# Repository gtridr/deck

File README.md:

# deck
An integrated instrument &amp; control surface based on norns

## Credits & Licensing

Starting things off: this project is licensed as a derivative work under GPL-3.0. All due credits to the following individuals & projects:

 - The core audio codec & voltage regulation design are unmodified from the 210330 revision of the [norns shield](https://github.com/monome/norns-shield) save for some rerouting & cleanup

 - The raspberry pi image is a very lightly modified fork of the mainline norns codebase, with just a few tweaks to map the 4th encoder, serial pins for MICROMIDITRS, and soft shutdown via ATXRaspi.

 - The teensy firmware is a fork of Okyeron's [DIY grid](https://github.com/okyeron/neotrellis-monome) firmware. All credit for the grid emulation goes to him; I've only added what was necessary to get the potentiometers working over USB MIDI

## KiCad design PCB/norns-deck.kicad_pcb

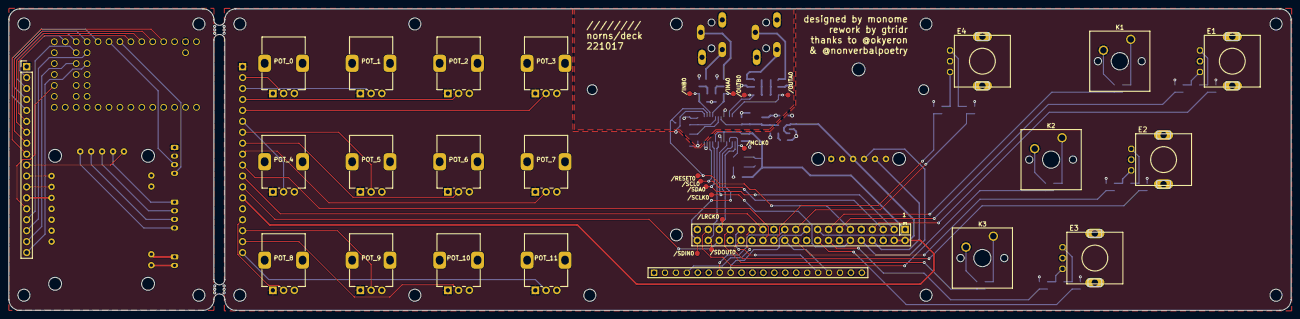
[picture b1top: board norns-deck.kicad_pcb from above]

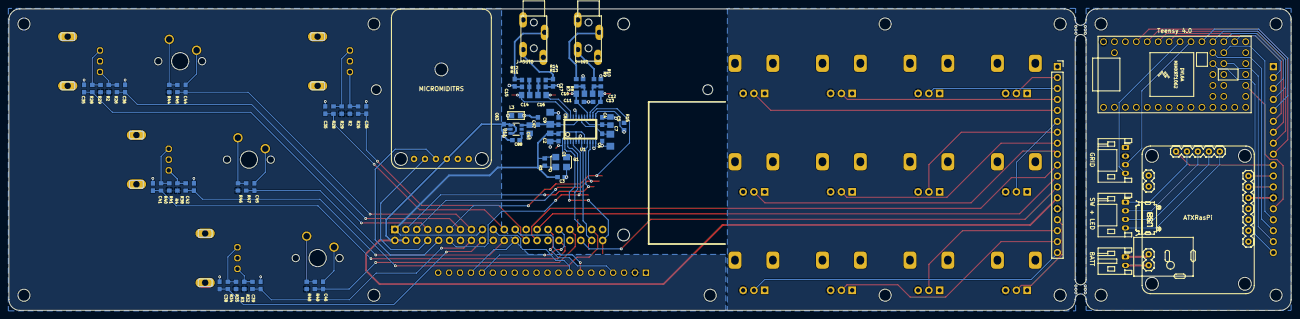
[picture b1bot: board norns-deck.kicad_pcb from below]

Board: 2 copper layers, 297.8 x 70.0 mm, 118 parts (76 on the bottom side), 80 nets.

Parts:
/INA0: TPTP12R; TP12R
/INB0: TPTP12R; TP12R
/LRCK0: TPTP12R; TP12R
/MCLK0: TPTP12R; TP12R
/OUTA0: TPTP12R; TP12R
/OUTB0: TPTP12R; TP12R
/RESET0: TPTP12R; TP12R
/SCL0: TPTP12R; TP12R
/SCLK0: TPTP12R; TP12R
/SDA0: TPTP12R; TP12R
/SDIN0: TPTP12R; TP12R
/SDOUT0: TPTP12R; TP12R
ATXRasPi: ATXRaspi
BATT: JST_PH_S2B-PH-K_1x02_P2.00mm_Horizontal
C1, C4, C6, C8, C47, C63: 100n; C0603
C2, C5, C10, C12, C43: 10u; C0805
C3, C35, C35#2, C36, C36#2, C38, C39, C41, C42, C44, C45, C46, C88: 10n; C0603
C7, C9: 47u; C1206
C11, C13: 220p COG; C0603
C14, C16: 3.3u; C0805
C15, C17: 2700p COG; C0603
DAUGHTERBOARD: PinSocket_1x18_P2.54mm_Vertical
E1: ENC1; PEC11RN
E2: ENC2; PEC11RN
E3: ENC3; PEC11RN
E4: ENC4; PEC11RN
GRID: JST_PH_S4B-PH-K_1x04_P2.00mm_Horizontal
J-IN0: JACK-TRS-SW; JACK4832.2330
J-OUT0: JACK-TRS-SW; JACK4832.2330
K1, K2, K3: SW_Cherry_MX_1.00u_PCB_NO_OUTLINE; SW_Cherry_MX_1.00u_PCB_NARROW_OUTLINE
L3: FERRITE; L0805
MICROMIDITRS: MICROMIDITRS
MNT: mounting hole
MNT#2, MNT#3, MNT#4, MNT#5, MNT#6: mounting hole
POT_0, POT_1, POT_2, POT_3, POT_4, POT_5, POT_6, POT_7, POT_8, POT_9, POT_10, POT_11: Potentiometer_Alps_RK09K_Single_Vertical
Q1: ASFL-12.288mhz; ASF
R1, R2, R2#2, R3, R4, R8, R10, R11, R13, R15, R26, R26#2, R28, R28#2, R29, R29#2, R32, R34, R35, R38, R40, R41, R44, R45, R46, R47, R48, R49: 10k; R0603
R7, R9: 4.99k; R0603
R12, R14: 590; R0603
SW + LED: JST_PH_S4B-PH-K_1x04_P2.00mm_Horizontal
Teensy 4.0: Teensy 4.0; Teensy40
U1: CS4270; TSSOP24
U11: TPS793; SSOP6
U$1: OLED128X64; OLED-ALEPH
X1: RASPI_BOARD_B+#_E3; RASPI_BOARD_B+_EDGES_3DRILL
mouse-bite-2.54mm-slot, mouse-bite-2.54mm-slot#2: VAL**; mouse-bite-2.54mm-slot

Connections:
+3V3: C1.1, C2.1, C3.1, Q1.4, R1.1, R2.2, R2#2.2, R3.2, R4.2, R29.2, R29#2.2, R35.2, R41.2, R44.1, R46.1, R48.1, U1.5, U1.8, U$1.2, X1.1, X1.17
+5V: ATXRasPi.9, C63.1, DAUGHTERBOARD.13, GRID.2, MICROMIDITRS.3, Teensy 4.0.33, U11.1, U11.3, X1.2, X1.4
A1: C35#2.1, R28#2.2, X1.7
A2: C41.1, R40.2, X1.32
A3: C38.1, R34.2, X1.18
A4: C35.1, R28.2, X1.21
A5V: C8.1, C9.1, C43.1, C47.1, U1.19, U11.6
AGND: C4.2, C5.2, C6.2, C7.2, C8.2, C9.2, C11.2, C13.2, C15.2, C17.2, C47.2, J-IN0.S, J-IN0.SW, J-OUT0.S, J-OUT0.SW, L3.1, R8.2, R10.2, R11.2, R13.2, U1.20
ATX1: DAUGHTERBOARD.10, X1.28
ATX2: DAUGHTERBOARD.11, X1.27
ATX3: DAUGHTERBOARD.12, X1.36
B1: C36.1, R26.2, X1.13
B2: C42.1, R38.2, X1.22
B3: C39.1, R32.2, X1.16
B4: C36#2.1, R26#2.2, X1.26
BAT+: ATXRasPi.14, BATT.2
BAT-: ATXRasPi.15, BATT.1
CE0: U$1.17, X1.24
GND: C1.2, C2.2, C3.2, C35.2, C35#2.2, C36.2, C36#2.2, C38.2, C39.2, C41.2, C42.2, C43.2, C44.2, C45.2, C46.2, C63.2, C88.2, DAUGHTERBOARD.1, E1.GND, E2.GND, E3.GND, GRID.1, K1.2, K2.2, K3.2, L3.2, MICROMIDITRS.1, POT_0.1, POT_1.1, POT_2.1, POT_3.1, POT_4.1, POT_5.1, POT_6.1, POT_7.1, POT_8.1, POT_9.1, POT_10.1, POT_11.1, Q1.2, R15.2, Teensy 4.0.32, U1.6, U1.11, U1.12, U1.13, U11.2, U$1.1, U$1.5, U$1.6, U$1.9, U$1.10, U$1.11, U$1.12, U$1.13, U$1.14, U$1.19, U$1.20, X1.6, X1.9, X1.14, X1.20, X1.25, X1.30, X1.34, X1.39
INA: /INA0.TP, C10.1, C11.1, U1.16
INB: /INB0.TP, C12.1, C13.1, U1.15
K1: C44.1, R45.2, X1.15
K2: C45.1, R47.2, X1.37
K3: C46.1, R49.2, X1.33
LED+: ATXRasPi.5, SW + LED.4
LED-: ATXRasPi.4, SW + LED.3
LRCK: /LRCK0.TP, U1.2, X1.35
MCLK: /MCLK0.TP, Q1.3, U1.3
MOSI: U$1.8, X1.19
unnamed: Q1.1, R1.2
unnamed: K1.1, R44.2, R45.1
unnamed: C4.1, C5.1, U1.17
unnamed: C6.1, C7.1, U1.18
unnamed: J-IN0.R, R7.2
unnamed: C10.2, R7.1, R8.1
unnamed: C12.2, R9.1, R10.1
unnamed: J-IN0.T, R9.2
unnamed: C16.2, R13.1, R14.1
unnamed: C14.2, R11.1, R12.1
unnamed: C15.1, J-OUT0.R, R12.2
unnamed: C17.1, J-OUT0.T, R14.2
unnamed: E1.A, R28#2.1, R29#2.1
unnamed: E1.B, R2.1, R26.1
unnamed: E3.B, R3.1, R32.1
unnamed: E3.A, R34.1, R35.1
unnamed: E2.B, R4.1, R38.1
unnamed: E2.A, R40.1, R41.1
unnamed: E4.A, R28.1, R29.1
unnamed: E4.B, R2#2.1, R26#2.1
unnamed: C88.1, U11.4
OUTA: /OUTA0.TP, C14.1, U1.23
OUTB: /OUTB0.TP, C16.1, U1.22
O_DC: U$1.4, X1.29
O_RESET: U$1.16, X1.31
R-CODEC: /RESET0.TP, R15.1, U1.14, X1.11
RX: MICROMIDITRS.4, X1.10
SCK: U$1.7, X1.23
SCL: /SCL0.TP, U1.10, X1.5
SCL0: GRID.4, Teensy 4.0.26
SCLK: /SCLK0.TP, U1.4, X1.12
SDA: /SDA0.TP, U1.9, X1.3
SDA0: GRID.3, Teensy 4.0.25
SDIN: /SDIN0.TP, U1.1, X1.40
SDOUT: /SDOUT0.TP, U1.7, X1.38
SW+: ATXRasPi.3, SW + LED.2
SW-: ATXRasPi.2, SW + LED.1
T+3v3: DAUGHTERBOARD.14, POT_0.3, POT_1.3, POT_2.3, POT_3.3, POT_4.3, POT_5.3, POT_6.3, POT_7.3, POT_8.3, POT_9.3, POT_10.3, POT_11.3, Teensy 4.0.16
TX: MICROMIDITRS.5, X1.8
p0: DAUGHTERBOARD.2, POT_0.2
p1: DAUGHTERBOARD.3, POT_1.2
p2: DAUGHTERBOARD.4, POT_2.2
p3: DAUGHTERBOARD.5, POT_3.2
p4: DAUGHTERBOARD.6, POT_4.2
p5: DAUGHTERBOARD.7, POT_5.2
p6: DAUGHTERBOARD.8, POT_6.2
p7: DAUGHTERBOARD.9, POT_7.2
p8: DAUGHTERBOARD.15, POT_8.2
p9: DAUGHTERBOARD.16, POT_9.2
p10: DAUGHTERBOARD.17, POT_10.2
p11: DAUGHTERBOARD.18, POT_11.2

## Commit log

2022-10-14 init
2022-10-15 RESTRUCTURE
2022-10-15 image rename
2022-10-15 readme update
2022-10-17 add gerbers
